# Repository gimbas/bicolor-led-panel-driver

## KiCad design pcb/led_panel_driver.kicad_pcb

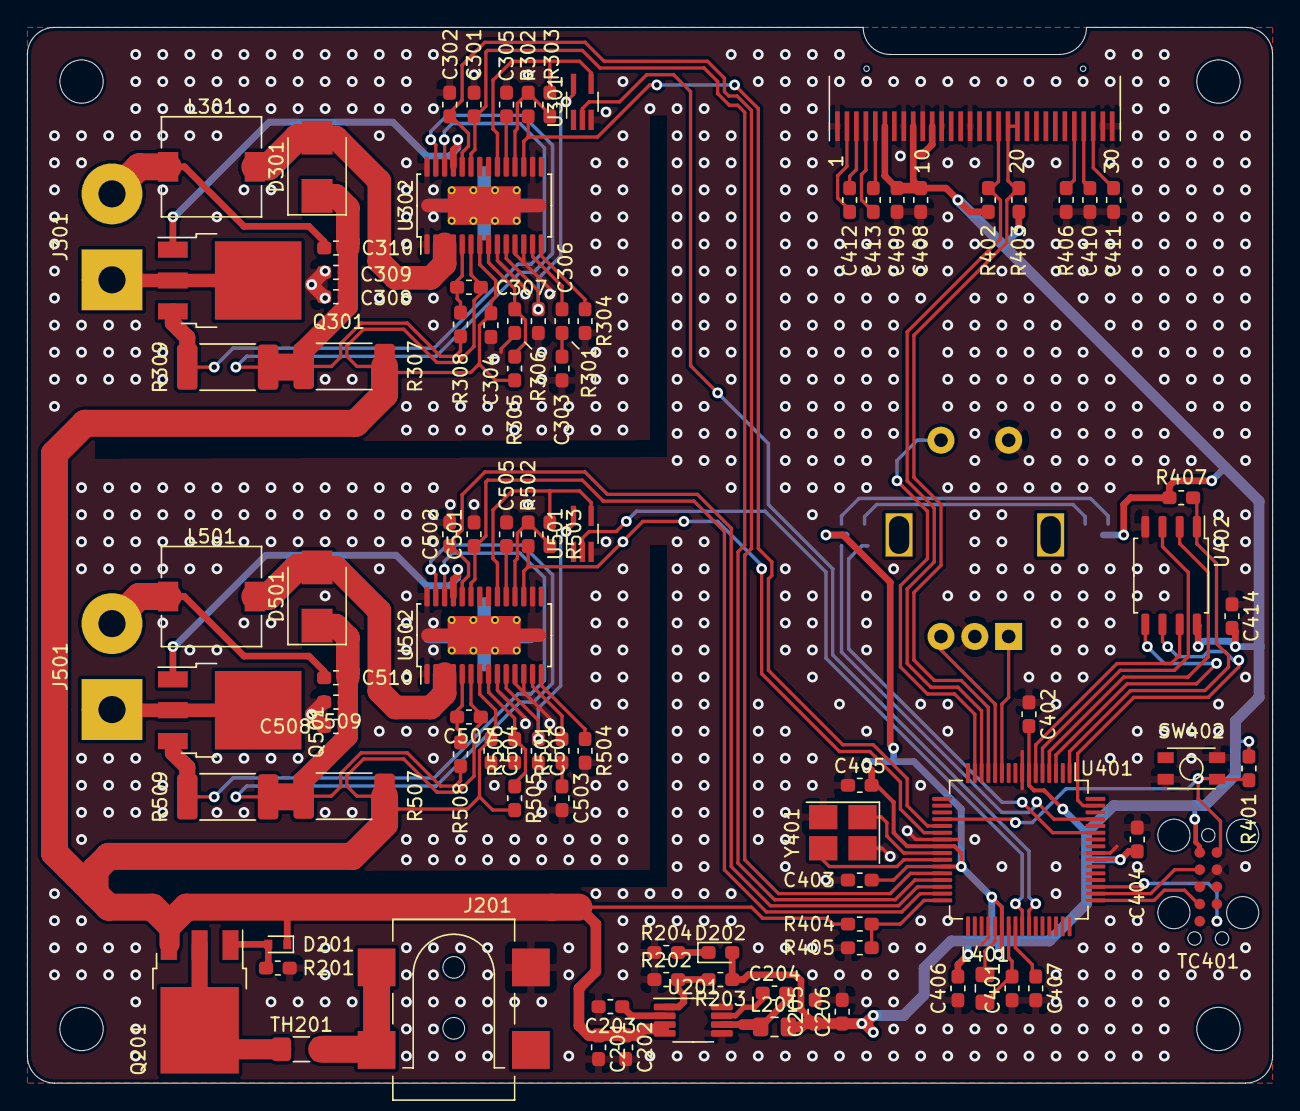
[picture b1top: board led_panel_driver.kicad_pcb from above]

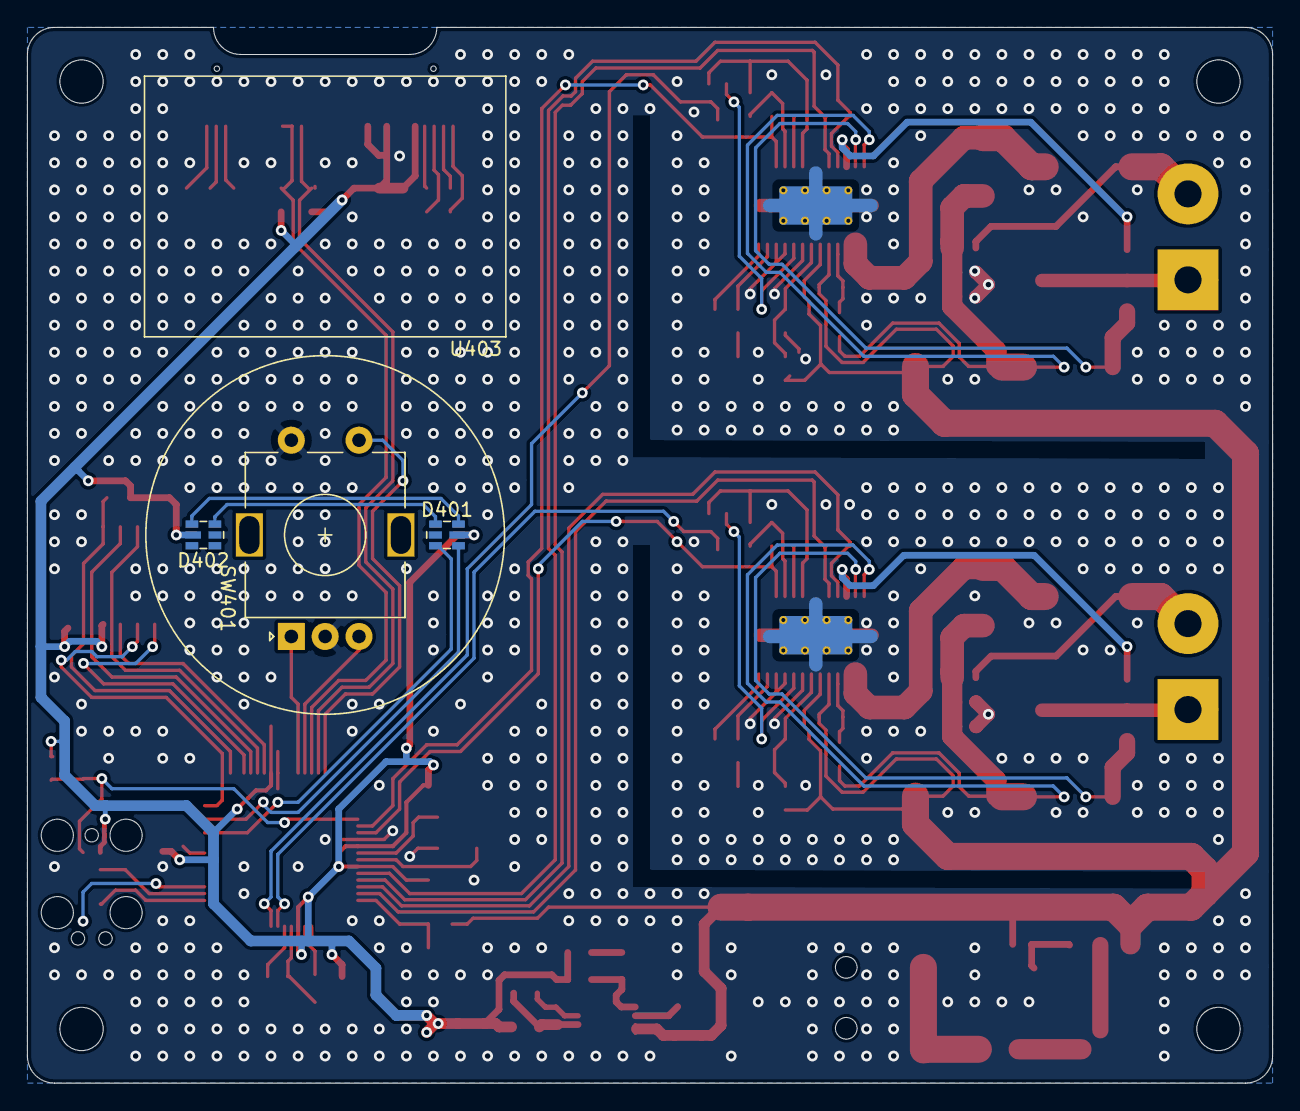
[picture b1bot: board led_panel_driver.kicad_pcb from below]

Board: 2 copper layers, 92.0 x 78.0 mm, 98 parts (4 on the bottom side), 81 nets.

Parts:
C201, C202, C205, C206, C411: 10uF; C_0603_1608Metric_Pad1.05x0.95mm_HandSolder
C203, C301, C302, C304, C406, C407, C501, C502, C504: 1uF; C_0603_1608Metric_Pad1.05x0.95mm_HandSolder
C204, C305, C402, C403, C404, C405, C414, C505: 100nF; C_0603_1608Metric_Pad1.05x0.95mm_HandSolder
C303, C503: 6.8nF; C_0603_1608Metric_Pad1.05x0.95mm_HandSolder
C306, C309, C408, C409, C410, C412, C413, C506, C509: 2u2F; C_0603_1608Metric_Pad1.05x0.95mm_HandSolder
C307, C507: DNP; C_0603_1608Metric_Pad1.05x0.95mm_HandSolder
C308, C310, C401, C508, C510: 4u7F; C_0603_1608Metric_Pad1.05x0.95mm_HandSolder
D201: 10V; D_SOD-523
D202: RED; LED_0603_1608Metric_Pad1.05x0.95mm_HandSolder
D301, D501: SK54; D_SMB
D401, D402: SK9822; SK9822-2020
J201: Barrel_Jack_Switch; BarrelJack_SMD
J301, J501: led_string_conn; SolderWirePad_1x02_P7.62mm_Drill2mm
L201: 15uH; L_0805_2012Metric_Pad1.15x1.40mm_HandSolder
L301, L501: 4u7H; L_7.3x7.3_H3.5
L401: 4u7H; L_0805_2012Metric_Pad1.15x1.40mm_HandSolder
Q201, Q301, Q501: AOD4185; TO-252-3_TabPin2
R201, R202, R401, R405: 10kΩ; R_0603_1608Metric_Pad1.05x0.95mm_HandSolder
R203: 31k6Ω; R_0603_1608Metric_Pad1.05x0.95mm_HandSolder
R204, R301, R501: 220Ω; R_0603_1608Metric_Pad1.05x0.95mm_HandSolder
R302, R303, R502, R503: DNP; R_0603_1608Metric_Pad1.05x0.95mm_HandSolder
R304, R504: 90k9Ω; R_0603_1608Metric_Pad1.05x0.95mm_HandSolder
R305, R505: 78k7Ω; R_0603_1608Metric_Pad1.05x0.95mm_HandSolder
R306, R506: 12k4Ω; R_0603_1608Metric_Pad1.05x0.95mm_HandSolder
R307, R507: 15mΩ; R_2512_6332Metric_Pad1.52x3.35mm_HandSolder
R308, R508: 0Ω; R_0603_1608Metric_Pad1.05x0.95mm_HandSolder
R309, R509: 62m5Ω; R_2512_6332Metric_Pad1.52x3.35mm_HandSolder
R402, R403: 4k7Ω; R_0603_1608Metric_Pad1.05x0.95mm_HandSolder
R404: 190kΩ; R_0603_1608Metric_Pad1.05x0.95mm_HandSolder
R406: 300kΩ; R_0603_1608Metric_Pad1.05x0.95mm_HandSolder
R407: 100kΩ; R_0603_1608Metric_Pad1.05x0.95mm_HandSolder
SW401: Rotary_Encoder_Switch; RotaryEncoder_Alps_EC11E-Switch_Vertical_H20mm
SW402: RST_BTN; btn_3x4x2mm_4p
TC401: TC-2050-IDC
TH201: 4A; Fuse_1206_3216Metric_Pad1.42x1.75mm_HandSolder
U201: MCP16311MS; MSOP-8_3x3mm_P0.65mm
U301, U501: SN74LVC1G07DCKR; SOT-353_SC-70-5_Handsoldering
U302, U502: LT3952A; HTSSOP-28-1EP_4.4x9.7mm_P0.65mm_EP2.85x5.4mm_ThermalVias
U401: EFM32GG1XB8XX-Q64; TQFP-64_10x10mm_P0.5mm
U402: QSPI-FLASH; SOIC-8_5.275x5.275mm_P1.27mm
U403: OLED_128x64; oled-132x64
Y401: 8MHz; Crystal_SMD_3225-4Pin_3.2x2.5mm_HandSoldering

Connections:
+3V3: C205.1, C206.1, C402.2, C403.2, C404.2, C405.2, C406.2, C408.1, C409.1, C414.2, D202.2, D401.5, D402.5, L201.2, R203.1, R401.2, R402.2, R403.2, R407.2, TC401.1, U401.7, U401.24, U401.27, U401.38, U401.55, U402.8, U403.6, U403.9, U403.11
/CONTROLLER/ENC_A: SW401.A, U401.11
/CONTROLLER/ENC_B: SW401.B, U401.12
/CONTROLLER/ENC_SW: SW401.S1, U401.15
/CONTROLLER/HF_XTAL_N: U401.26, Y401.3
/CONTROLLER/HF_XTAL_P: U401.25, Y401.1
/CONTROLLER/LED_CKI: D401.4, U401.61
/CONTROLLER/LED_SDI: D401.3, U401.59
/CONTROLLER/MCU_RST: R401.1, SW402.1, TC401.10, U401.20
/CONTROLLER/OLED_SCL: R402.1, U401.14, U403.18
/CONTROLLER/OLED_SDA: R403.1, U401.13, U403.19, U403.20
/CONTROLLER/QSPI_CLK: U401.63, U402.6
/CONTROLLER/QSPI_D0: U401.3, U402.5
/CONTROLLER/QSPI_D1: U401.4, U402.2
/CONTROLLER/QSPI_D2: U401.5, U402.3
/CONTROLLER/QSPI_D3: U401.6, U402.7
/CONTROLLER/QSPI_~CS: R407.1, U401.1, U402.1
/CONTROLLER/SWCLK: TC401.4, U401.49
/CONTROLLER/SWDIO: TC401.2, U401.50
/CONTROLLER/SWO: TC401.6, U401.51
/CONTROLLER/VBUS: C201.1, C202.1, C304.1, C307.1, C504.1, C507.1, D201.1, Q201.3, R305.2, R307.1, R404.2, R505.2, R507.1, U201.3, U201.4, U302.6, U302.7, U502.6, U502.7
/CONTROLLER/VBUS_SCALED: R404.1, R405.2, U401.32
/LED_CONTROLLER_C/IIN: C301.1, U302.23, U401.29
/LED_CONTROLLER_C/ILED: C302.1, U302.24, U401.28
/LED_CONTROLLER_C/INTVCC: C306.1, U301.5, U302.10
/LED_CONTROLLER_C/ISET: R302.2, U302.17, U401.21
/LED_CONTROLLER_C/PWM: U301.2, U401.42
/sheet5EA750BF/IIN: C501.1, U401.31, U502.23
/sheet5EA750BF/ILED: C502.1, U401.30, U502.24
/sheet5EA750BF/INTVCC: C506.1, U501.5, U502.10
/sheet5EA750BF/ISET: R502.2, U401.22, U502.17
/sheet5EA750BF/PWM: U401.41, U501.2
GND: C201.2, C202.2, C203.2, C205.2, C206.2, C301.2, C302.2, C303.2, C304.2, C305.2, C306.2, C308.2, C309.2, C401.1, C402.1, C403.1, C404.1, C405.1, C406.1, C407.2, C408.2, C409.2, C410.1, C411.1, C414.1, C501.2, C502.2, C503.2, C504.2, C505.2, C506.2, C508.2, C509.2, D401.2, D402.2, J201.2, R201.1, R202.1, R204.1, R304.2, R306.1, R405.1, R406.2, R504.2, R506.1, SW401.C, SW401.S2, SW402.2, SW402.4, TC401.3, TC401.9, U201.5, U201.8, U301.3, U302.1, U302.9, U302.11, U302.12, U302.16, U302.28, U302.29, U401.8, U401.23, U401.36, U401.56, U402.4, U403.1, U403.8, U403.10, U403.12, U403.15, U403.29, U403.30, U501.3, U502.1, U502.9, U502.11, U502.12, U502.16, U502.28, U502.29, Y401.2, Y401.4
unnamed: C203.1, U201.2
unnamed: C204.1, U201.7
unnamed: C204.2, L201.1, U201.6
unnamed: C303.1, R301.1
unnamed: C305.1, U302.19
unnamed: C307.2, R308.1, U302.5
unnamed: C308.1, C309.1, C310.1, D301.1, R307.2, R308.2, R309.1, U302.27
unnamed: C310.2, J301.2, L301.1
unnamed: C401.2, L401.1, U401.39
unnamed: C407.1, U401.40
unnamed: C410.2, U403.27
unnamed: C411.2, U403.28
unnamed: C412.1, U403.3
unnamed: C412.2, U403.2
unnamed: C413.1, U403.5
unnamed: C413.2, U403.4
unnamed: C503.1, R501.1
unnamed: C505.1, U502.19
unnamed: C507.2, R508.1, U502.5
unnamed: C508.1, C509.1, C510.1, D501.1, R507.2, R508.2, R509.1, U502.27
unnamed: C510.2, J501.2, L501.1
unnamed: D201.2, Q201.1, R201.2
unnamed: D202.1, R204.2
unnamed: D301.2, L301.2, U302.2, U302.3, U302.4
unnamed: D401.1, D402.3
unnamed: D401.6, D402.4
unnamed: D501.2, L501.2, U502.2, U502.3, U502.4
unnamed: J201.1, TH201.2
unnamed: J301.1, Q301.2
unnamed: J501.1, Q501.2
unnamed: L401.2, U401.37
unnamed: Q201.2, TH201.1
unnamed: Q301.1, U302.25
unnamed: Q301.3, R309.2, U302.26
unnamed: Q501.1, U502.25
unnamed: Q501.3, R509.2, U502.26
unnamed: R202.2, R203.2, U201.1
unnamed: R301.2, U302.13
unnamed: R302.1, R303.1, U302.18
unnamed: R303.2, U301.4, U302.20
unnamed: R304.1, U302.14
unnamed: R305.1, R306.2, U302.8
unnamed: R406.1, U403.26
unnamed: R501.2, U502.13
unnamed: R502.1, R503.1, U502.18
unnamed: R503.2, U501.4, U502.20
unnamed: R504.1, U502.14
unnamed: R505.1, R506.2, U502.8

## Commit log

2020-04-16 pcb: upload
2020-04-16 pcb: move to new dir
2020-07-30 stashed
